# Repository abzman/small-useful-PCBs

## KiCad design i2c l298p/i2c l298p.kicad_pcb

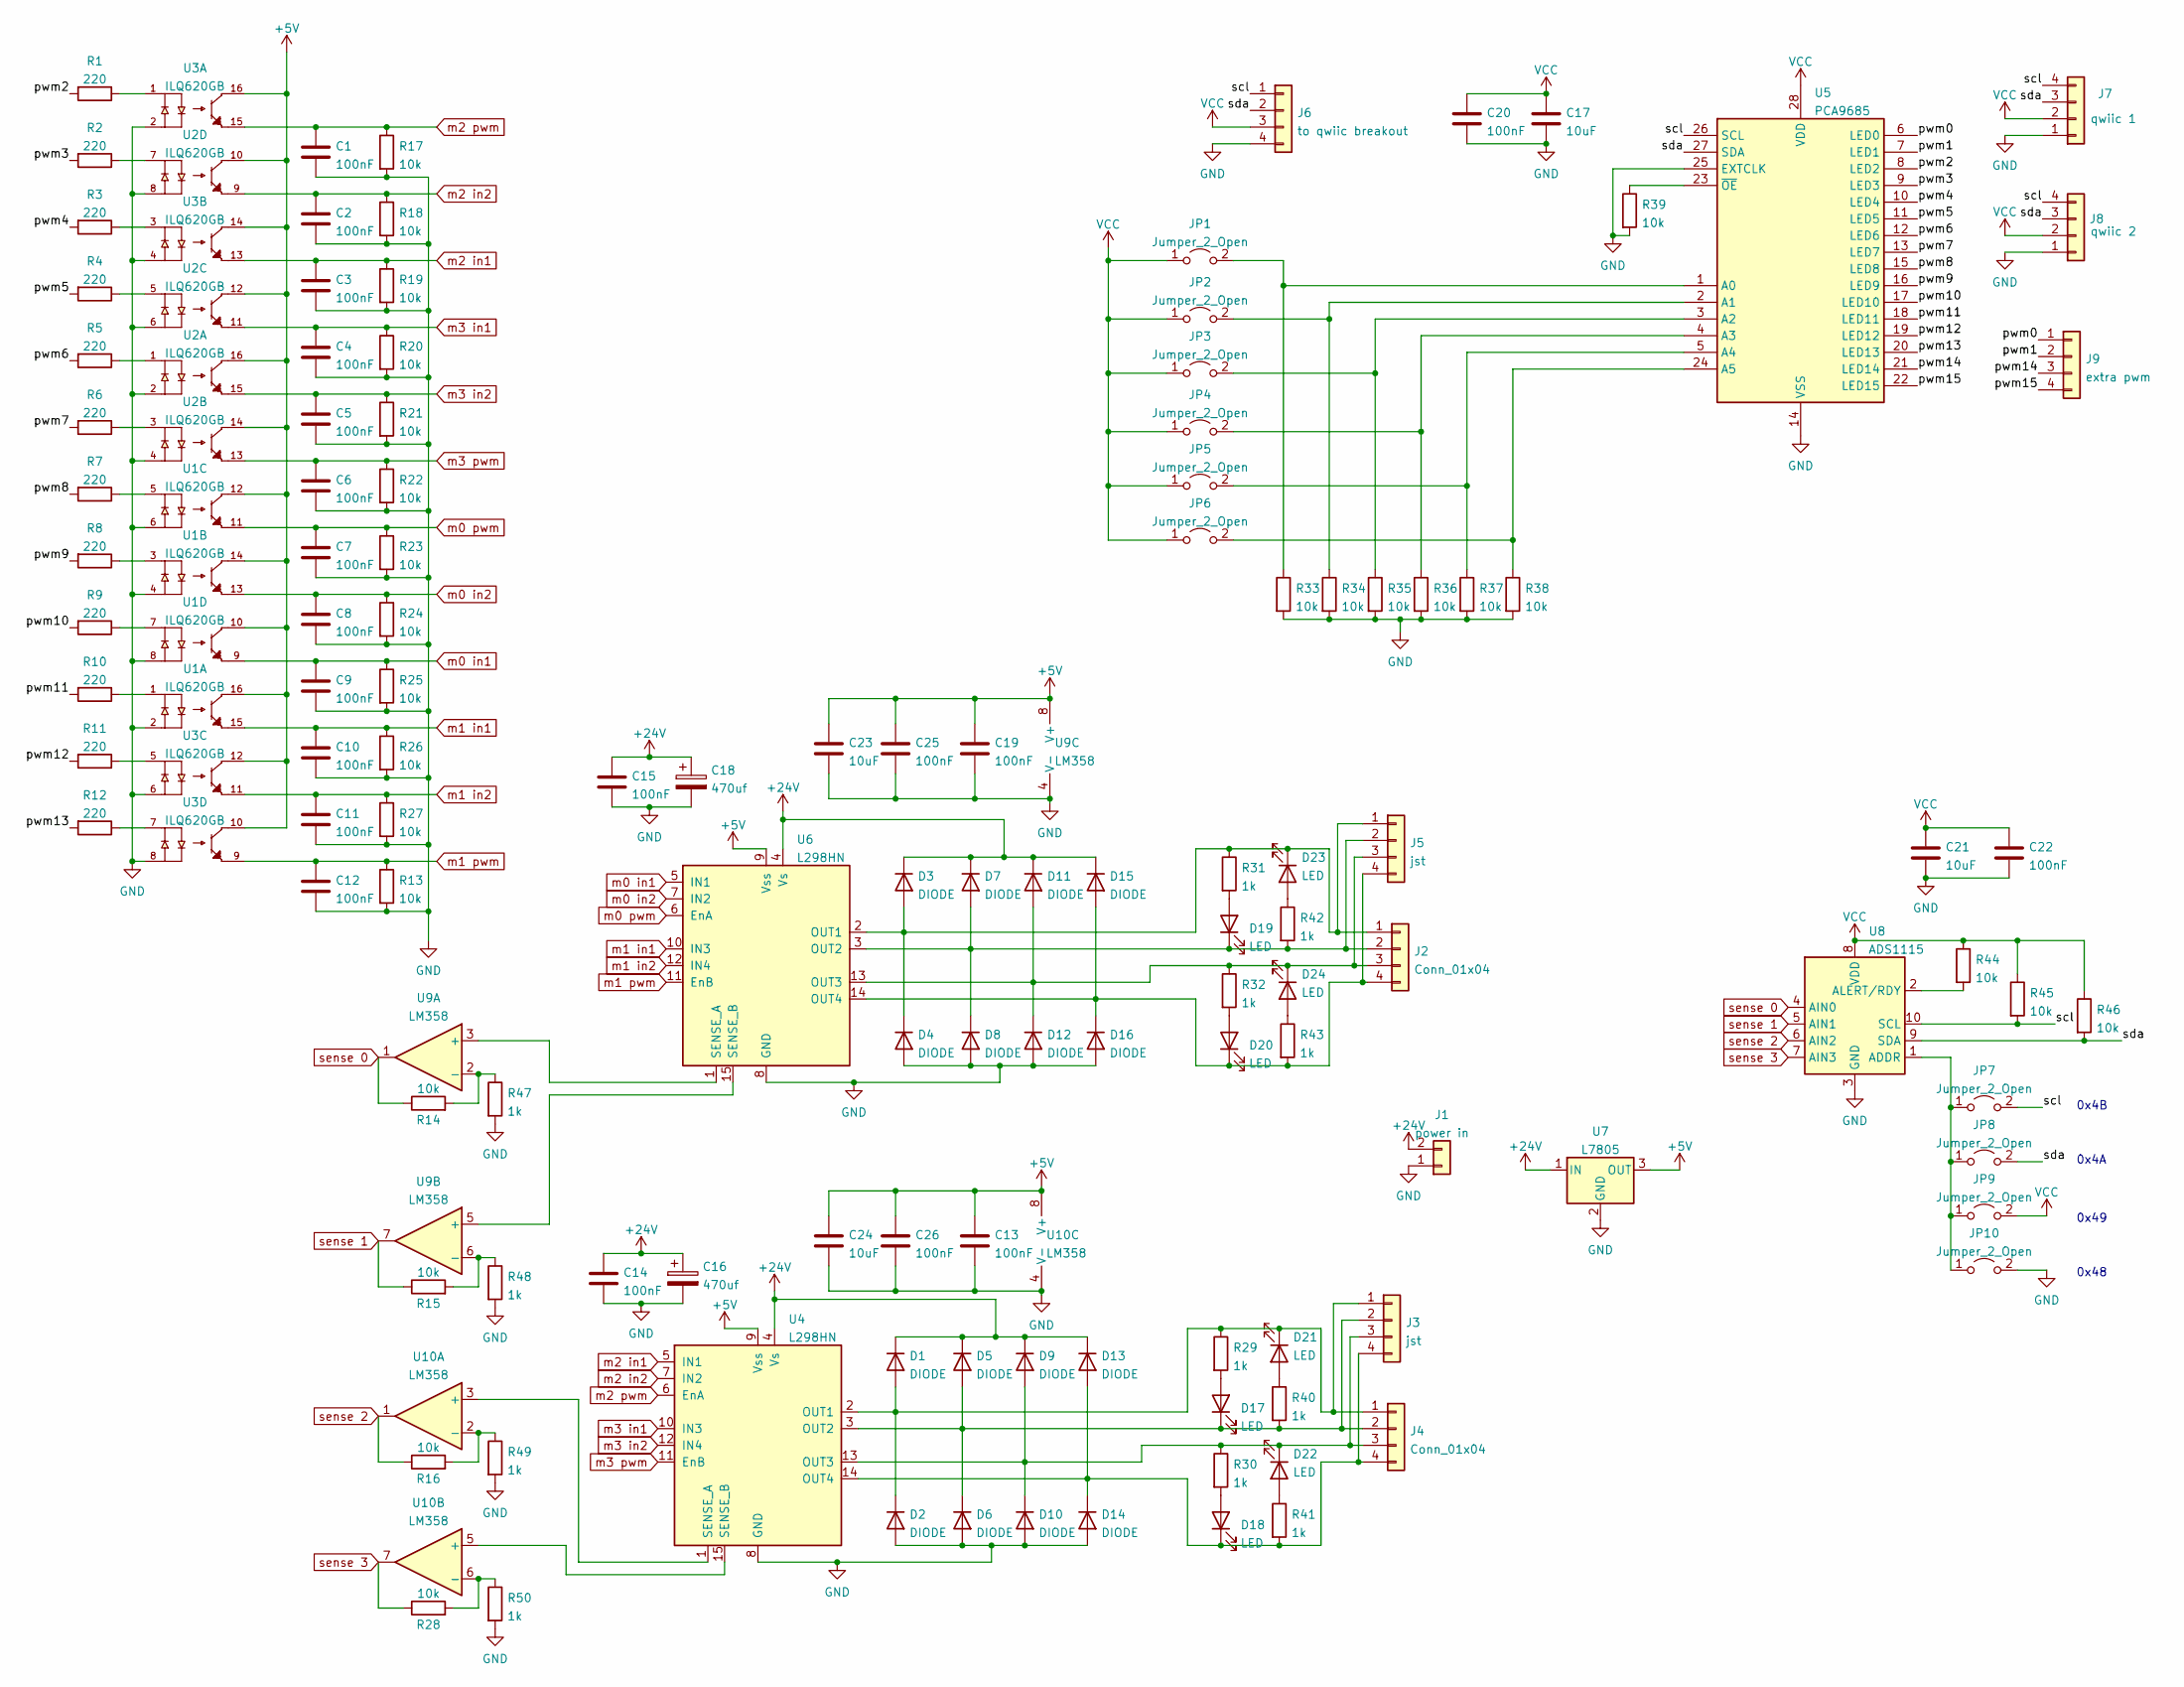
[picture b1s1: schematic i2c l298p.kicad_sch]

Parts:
C1, C2, C3, C4, C5, C6, C7, C8, C9, C10, C11, C12, C13, C14, C15, C19, C20, C22, C25, C26: 100nF; C_0603_1608Metric
C16, C18: 470uf; CP_Radial_D8.0mm_P3.50mm
C17, C21, C23, C24: 10uF; C_0603_1608Metric
D1, D2, D3, D4, D5, D6, D7, D8, D9, D10, D11, D12, D13, D14, D15, D16: DIODE; D_SMA
D17, D18, D19, D20, D21, D22, D23, D24: LED; LED_0603_1608Metric
J1: power in; TerminalBlock_Phoenix_MKDS-1,5-2_1x02_P5.00mm_Horizontal
J2, J4: Conn_01x04; TerminalBlock_Phoenix_MKDS-1,5-4_1x04_P5.00mm_Horizontal
J3, J5: jst; JST_XH_B4B-XH-A_1x04_P2.50mm_Vertical
J6: to qwiic breakout; PinHeader_1x04_P2.54mm_Vertical
J7: qwiic 1; JST_SH_SM04B-SRSS-TB_1x04-1MP_P1.00mm_Horizontal
J8: qwiic 2; JST_SH_SM04B-SRSS-TB_1x04-1MP_P1.00mm_Horizontal
J9: extra pwm; PinHeader_1x04_P2.54mm_Vertical
JP1, JP2, JP3, JP4, JP5, JP7, JP8, JP9, JP10: Jumper_2_Open; SolderJumper-2_P1.3mm_Open_RoundedPad1.0x1.5mm
JP6: Jumper_2_Open; SolderJumper-2_P1.3mm_Bridged_RoundedPad1.0x1.5mm
R1, R2, R3, R4, R5, R6, R7, R8, R9, R10, R11, R12: 220; R_0603_1608Metric
R13, R14, R15, R16, R17, R18, R19, R20, R21, R22, R23, R24, R25, R26, R27, R28, R33, R34, R35, R36, R37, R38, R39, R44, R45, R46: 10k; R_0603_1608Metric
R29, R30, R31, R32, R40, R41, R42, R43, R47, R48, R49, R50: 1k; R_0603_1608Metric
U1, U2, U3: ILQ620GB; OPTO_ILQ620GB-X009; PARTREV 1.8
U4, U6: L298HN; TO-220-15_P2.54x2.54mm_StaggerOdd_Lead4.58mm_Vertical
U5: PCA9685; TSSOP-28_4.4x9.7mm_P0.65mm
U7: L7805; TO-220-3_Horizontal_TabDown
U8: ADS1115; TSSOP-10_3x3mm_P0.5mm
U9, U10: LM358; SOIC-8_3.9x4.9mm_P1.27mm

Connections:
+5V: C13.1, C19.1, C23.1, C24.1, C25.1, C26.1, U1.10, U1.12, U1.14, U1.16, U2.10, U2.12, U2.14, U2.16, U3.10, U3.12, U3.14, U3.16, U4.9 (Vss), U6.9 (Vss), U7.3 (OUT), U9.8 (V+), U10.8 (V+)
+24V: C14.1, C15.1, C16.1, C18.1, D1.2 (K), D3.2 (K), D5.2 (K), D7.2 (K), D9.2 (K), D11.2 (K), D13.2 (K), D15.2 (K), J1.2, U4.4 (Vs), U6.4 (Vs), U7.1 (IN)
/pwm0: J9.1, U5.6 (LED0)
/pwm1: J9.2, U5.7 (LED1)
/pwm2: R1.2, U5.8 (LED2)
/pwm3: R2.2, U5.9 (LED3)
/pwm4: R3.2, U5.10 (LED4)
/pwm5: R4.2, U5.11 (LED5)
/pwm6: R5.2, U5.12 (LED6)
/pwm7: R6.2, U5.13 (LED7)
/pwm8: R7.2, U5.15 (LED8)
/pwm9: R8.2, U5.16 (LED9)
/pwm10: R9.2, U5.17 (LED10)
/pwm11: R10.2, U5.18 (LED11)
/pwm12: R11.2, U5.19 (LED12)
/pwm13: R12.2, U5.20 (LED13)
/pwm14: J9.3, U5.21 (LED14)
/pwm15: J9.4, U5.22 (LED15)
/scl: J6.1, J7.4, J8.4, JP7.2 (B), R45.2, U5.26 (SCL), U8.10 (SCL)
/sda: J6.2, J7.3, J8.3, JP8.2 (B), R46.2, U5.27 (SDA), U8.9 (SDA)
GND: C1.2, C2.2, C3.2, C4.2, C5.2, C6.2, C7.2, C8.2, C9.2, C10.2, C11.2, C12.2, C13.2, C14.2, C15.2, C16.2, C17.2, C18.2, C19.2, C20.2, C21.2, C22.2, C23.2, C24.2, C25.2, C26.2, D2.1 (A), D4.1 (A), D6.1 (A), D8.1 (A), D10.1 (A), D12.1 (A), D14.1 (A), D16.1 (A), J1.1, J6.4, J7.1, J8.1, JP10.2 (B), R13.2, R17.2, R18.2, R19.2, R20.2, R21.2, R22.2, R23.2, R24.2, R25.2, R26.2, R27.2, R33.2, R34.2, R35.2, R36.2, R37.2, R38.2, R39.2, R47.2, R48.2, R49.2, R50.2, U1.2, U1.4, U1.6, U1.8, U2.2, U2.4, U2.6, U2.8, U3.2, U3.4, U3.6, U3.8, U4.8 (GND), U5.14 (VSS), U5.25 (EXTCLK), U6.8 (GND), U7.2 (GND), U8.3 (GND), U9.4 (V-), U10.4 (V-)
unnamed: D1.1 (A), D2.2 (K), D21.1 (K), J3.1, J4.1, R29.1, U4.2 (OUT1)
unnamed: D9.1 (A), D10.2 (K), D22.1 (K), J3.3, J4.3, R30.1, U4.13 (OUT3)
unnamed: D11.1 (A), D12.2 (K), D24.1 (K), J2.3, J5.3, R32.1, U6.13 (OUT3)
unnamed: D13.1 (A), D14.2 (K), D18.1 (K), J3.4, J4.4, R41.2, U4.14 (OUT4)
unnamed: D15.1 (A), D16.2 (K), D20.1 (K), J2.4, J5.4, R43.2, U6.14 (OUT4)
unnamed: D5.1 (A), D6.2 (K), D17.1 (K), J3.2, J4.2, R40.2, U4.3 (OUT2)
unnamed: D17.2 (A), R29.2
unnamed: D18.2 (A), R30.2
unnamed: D7.1 (A), D8.2 (K), D19.1 (K), J2.2, J5.2, R42.2, U6.3 (OUT2)
unnamed: D19.2 (A), R31.2
unnamed: D20.2 (A), R32.2
unnamed: D21.2 (A), R40.1
unnamed: D22.2 (A), R41.1
unnamed: D3.1 (A), D4.2 (K), D23.1 (K), J2.1, J5.1, R31.1, U6.2 (OUT1)
unnamed: D23.2 (A), R42.1
unnamed: D24.2 (A), R43.1
unnamed: JP1.2 (B), R33.1, U5.1 (A0)
unnamed: JP2.2 (B), R34.1, U5.2 (A1)
unnamed: JP3.2 (B), R35.1, U5.3 (A2)
unnamed: JP4.2 (B), R36.1, U5.4 (A3)
unnamed: JP5.2 (B), R37.1, U5.5 (A4)
unnamed: JP6.2 (B), R38.1, U5.24 (A5)
unnamed: JP7.1 (A), JP8.1 (A), JP9.1 (A), JP10.1 (A), U8.1 (ADDR)
unnamed: R1.1, U3.1
unnamed: R2.1, U2.7
unnamed: R3.1, U3.3
unnamed: R4.1, U2.5
unnamed: R5.1, U2.1
unnamed: R6.1, U2.3
unnamed: R7.1, U1.5
unnamed: R8.1, U1.3
unnamed: R9.1, U1.7
unnamed: R10.1, U1.1
unnamed: R11.1, U3.5
unnamed: R12.1, U3.7
unnamed: R14.2, R47.1, U9.2 (-)
unnamed: R15.2, R48.1, U9.6 (-)
unnamed: R16.2, R49.1, U10.2 (-)
unnamed: R28.2, R50.1, U10.6 (-)
unnamed: R39.1, U5.23 (~OE)
unnamed: R44.2, U8.2 (ALERT/RDY)
unnamed: U6.1 (SENSE_A), U9.3 (+)
unnamed: U6.15 (SENSE_B), U9.5 (+)
unnamed: U4.1 (SENSE_A), U10.3 (+)
unnamed: U4.15 (SENSE_B), U10.5 (+)
VCC: C17.1, C20.1, C21.1, C22.1, J6.3, J7.2, J8.2, JP1.1 (A), JP2.1 (A), JP3.1 (A), JP4.1 (A), JP5.1 (A), JP6.1 (A), JP9.2 (B), R44.1, R45.1, R46.1, U5.28 (VDD), U8.8 (VDD)
m0 in1: C9.1, R25.1, U1.9, U6.5 (IN1)
m0 in2: C8.1, R24.1, U1.13, U6.7 (IN2)
m0 pwm: C7.1, R23.1, U1.11, U6.6 (EnA)
m1 in1: C10.1, R26.1, U1.15, U6.10 (IN3)
m1 in2: C11.1, R27.1, U3.11, U6.12 (IN4)
m1 pwm: C12.1, R13.1, U3.9, U6.11 (EnB)
m2 in1: C3.1, R19.1, U3.13, U4.5 (IN1)
m2 in2: C2.1, R18.1, U2.9, U4.7 (IN2)
m2 pwm: C1.1, R17.1, U3.15, U4.6 (EnA)
m3 in1: C4.1, R20.1, U2.11, U4.10 (IN3)
m3 in2: C5.1, R21.1, U2.15, U4.12 (IN4)
m3 pwm: C6.1, R22.1, U2.13, U4.11 (EnB)
sense 0: R14.1, U8.4 (AIN0), U9.1
sense 1: R15.1, U8.5 (AIN1), U9.7
sense 2: R16.1, U8.6 (AIN2), U10.1
sense 3: R28.1, U8.7 (AIN3), U10.7

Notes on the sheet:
0x48
0x4A
0x49
0x4B

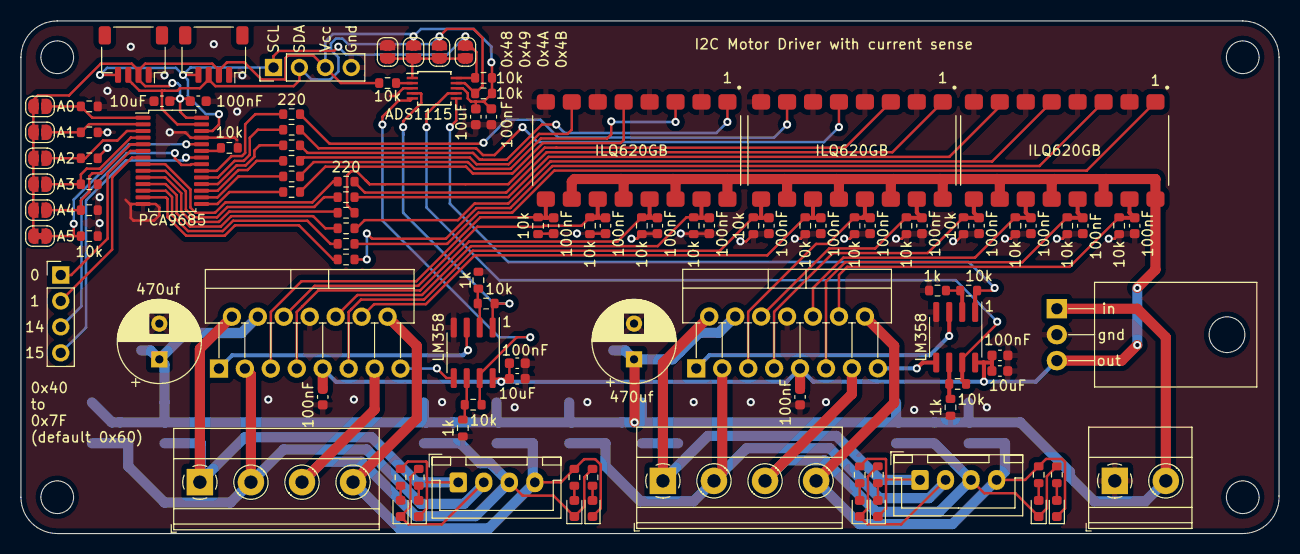
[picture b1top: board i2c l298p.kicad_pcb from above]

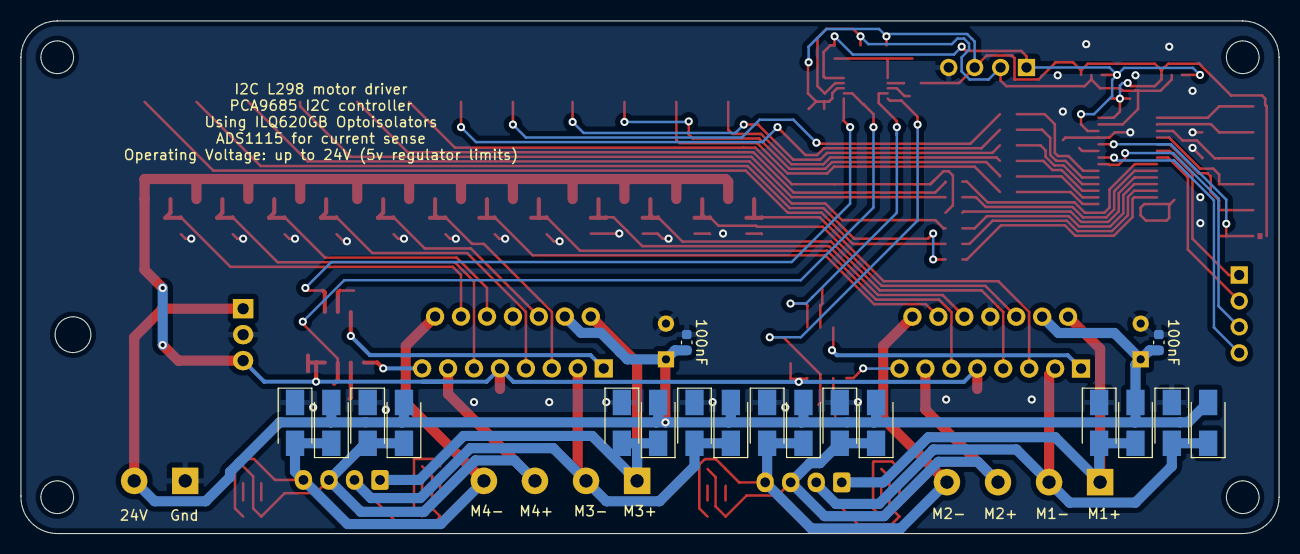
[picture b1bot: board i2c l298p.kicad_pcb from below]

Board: 2 copper layers, 123.2 x 50.2 mm, 129 parts (18 on the bottom side), 83 nets.

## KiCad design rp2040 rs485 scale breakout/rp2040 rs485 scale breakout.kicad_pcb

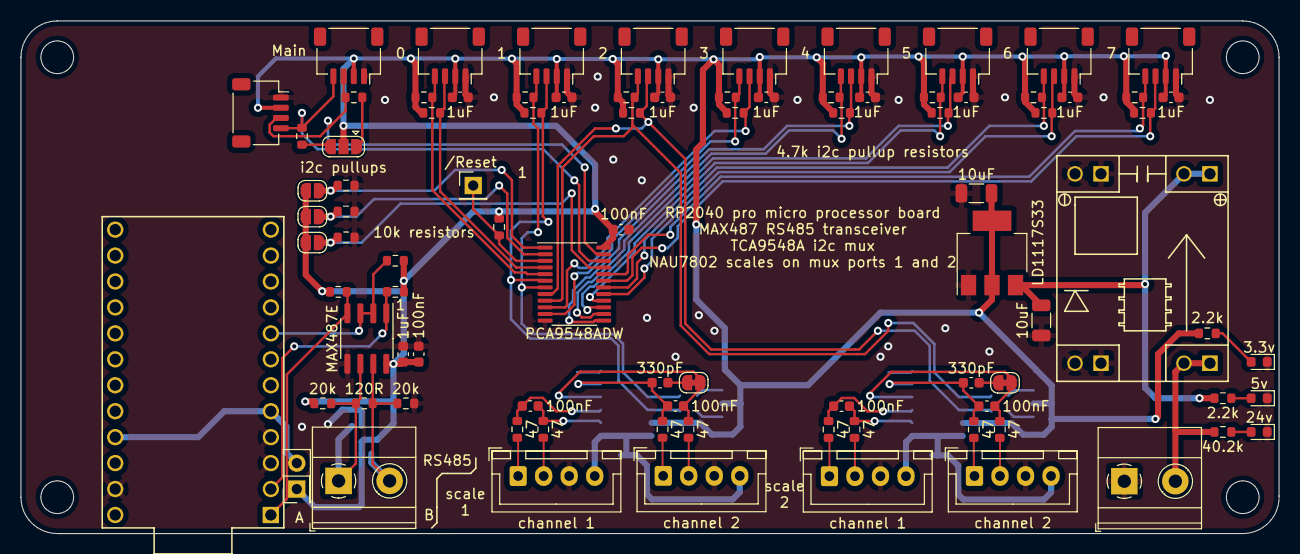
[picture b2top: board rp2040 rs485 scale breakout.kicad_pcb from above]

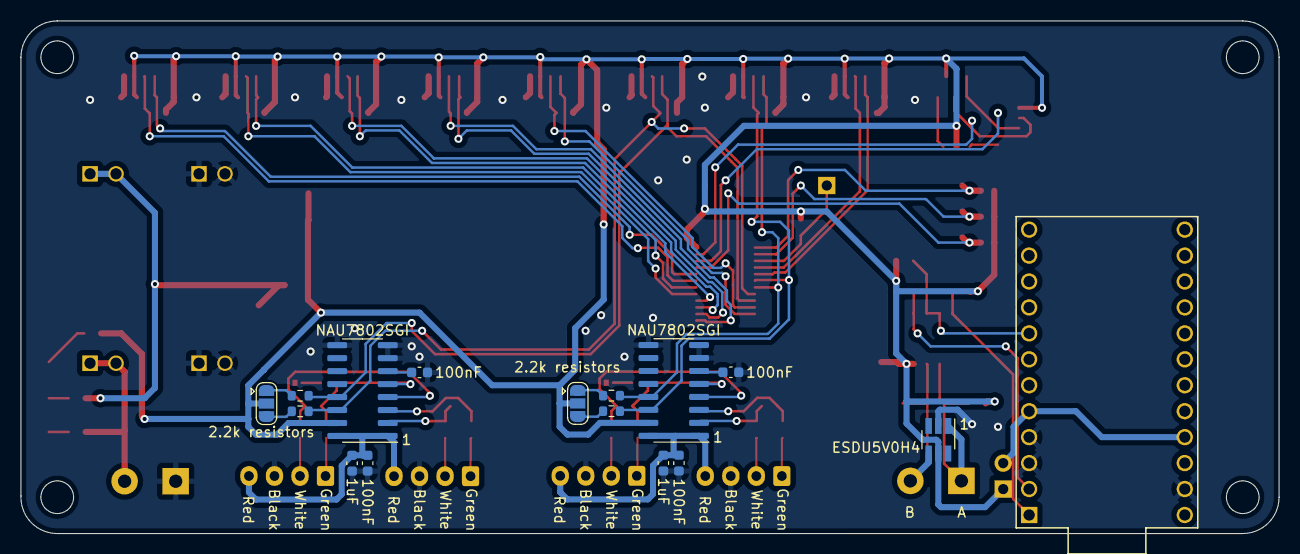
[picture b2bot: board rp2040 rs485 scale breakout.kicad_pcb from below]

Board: 2 copper layers, 123.2 x 50.2 mm, 105 parts (15 on the bottom side), 63 nets.

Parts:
C1, C4, C5, C6, C7, C8, C9, C10, C11, C16, C21: 1uF; C_0603_1608Metric
C2, C3, C13, C14, C15, C18, C19, C20, C22, C23: 100nF; C_0603_1608Metric
C12, C17: 330pF; C_0603_1608Metric
C24, C25: 10uF; C_1206_3216Metric
D1: 24v; LED_0603_1608Metric
D2: 5v; LED_0603_1608Metric
D3: 3.3v; LED_0603_1608Metric
J1: main i2c; JST_SH_SM04B-SRSS-TB_1x04-1MP_P1.00mm_Horizontal
J2: ESDU5V0H4; SOT-23-6_Handsoldering
J3: rs485; TerminalBlock_Phoenix_MKDS-1,5-2_1x02_P5.00mm_Horizontal
J4: Conn_01x01; PinHeader_1x01_P2.54mm_Vertical
J5: i2c pullups; SolderJumper-3_P1.3mm_Open_RoundedPad1.0x1.5mm
J6: qwiic from pro micro; JST_SH_SM04B-SRSS-TB_1x04-1MP_P1.00mm_Horizontal
J7: i2c 5; JST_SH_SM04B-SRSS-TB_1x04-1MP_P1.00mm_Horizontal
J8: i2c 6; JST_SH_SM04B-SRSS-TB_1x04-1MP_P1.00mm_Horizontal
J9: i2c 7; JST_SH_SM04B-SRSS-TB_1x04-1MP_P1.00mm_Horizontal
J10: i2c 3; JST_SH_SM04B-SRSS-TB_1x04-1MP_P1.00mm_Horizontal
J11: i2c 4; JST_SH_SM04B-SRSS-TB_1x04-1MP_P1.00mm_Horizontal
J12: i2c 2; JST_SH_SM04B-SRSS-TB_1x04-1MP_P1.00mm_Horizontal
J13: i2c 0; JST_SH_SM04B-SRSS-TB_1x04-1MP_P1.00mm_Horizontal
J14: i2c 1; JST_SH_SM04B-SRSS-TB_1x04-1MP_P1.00mm_Horizontal
J15, J19: channel 1; JST_XH_B4B-XH-A_1x04_P2.50mm_Vertical
J16, J20: channel 2; JST_XH_B4B-XH-A_1x04_P2.50mm_Vertical
J17, J21: cap; SolderJumper-2_P1.3mm_Bridged_RoundedPad1.0x1.5mm
J18, J22: i2c pullips; SolderJumper-3_P1.3mm_Open_RoundedPad1.0x1.5mm
J23: power in; TerminalBlock_Phoenix_MKDS-1,5-2_1x02_P5.00mm_Horizontal
J24: Conn_01x02; PinHeader_2x01_P2.54mm_Vertical
JP1, JP2, JP3: Jumper_2_Open; SolderJumper-2_P1.3mm_Open_RoundedPad1.0x1.5mm
R1, R2, R3, R4, R8, R9, R10: 10k; R_0603_1608Metric
R5, R7: 20k; R_0603_1608Metric
R6: 120R; R_0603_1608Metric
R11, R12, R13, R14, R15, R16, R17, R18, R19, R20, R21, R22, R23, R24, R25, R26, R27, R28: 4.7k; R_0603_1608Metric
R29, R30, R33, R34, R37, R38, R39, R40: 47; R_0603_1608Metric
R31, R32, R35, R36, R42, R43: 2.2k; R_0603_1608Metric
R41: 40.2k; R_0603_1608Metric
U1: MAX487E; SOIC-8_3.9x4.9mm_P1.27mm
U2: ProMicro_2040; ProMicro
U3: PCA9548ADW; TSSOP-24_4.4x7.8mm_P0.65mm
U4, U5: NAU7802SGI; SOIC-16_3.9x9.9mm_P1.27mm
U6: mp1584 dcdc; MP1584_buck_module
U7: LD1117S33; SOT-223-3_TabPin2

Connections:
485 direction: R2.2, U1.2 (~RE), U1.3 (DE), U2.8 (5)
+3V3: C1.1, C2.1, C3.1, C4.1, C5.1, C6.1, C7.1, C8.1, C9.1, C10.1, C11.1, C25.1, J1.2, J2.5, J5.2, J6.2, J7.2, J8.2, J9.2, J10.2, J11.2, J12.2, J13.2, J14.2, J18.2, J22.2, J24.1, JP1.1 (A), JP2.1 (A), JP3.1 (A), R1.1, R2.1, R3.1, R7.2, R10.1, R13.1, R14.1, R15.1, R16.1, R17.1, R18.1, R19.1, R20.1, R21.1, R22.1, R23.1, R24.1, R25.1, R26.1, R27.1, R28.1, R43.1, U1.8 (VCC), U3.24 (VCC), U4.15 (DVDD), U5.15 (DVDD), U7.2 (VO)
+5V: C24.1, R42.1, U6.4, U7.3 (VI)
+24V: J23.2, R41.1, U6.1
/nau7802 module1/A+: J19.1, R34.1
/nau7802 module1/A-: J19.2, R33.1
/nau7802 module1/B+: J20.1, R40.1
/nau7802 module1/B-: J20.2, R39.1
/nau7802 module/A+: J15.1, R30.1
/nau7802 module/A-: J15.2, R29.1
/nau7802 module/B+: J16.1, R38.1
/nau7802 module/B-: J16.2, R37.1
A: J2.1, J3.1, R6.2, R7.1, U1.6 (A)
A0: JP1.2 (B), R4.1, U3.1 (A0)
A1: JP2.2 (B), R8.1, U3.2 (A1)
A2: JP3.2 (B), R9.1, U3.21 (A2)
B: J2.4, J3.2, R5.2, R6.1, U1.7 (B)
GND: C1.2, C2.2, C3.2, C4.2, C5.2, C6.2, C7.2, C8.2, C9.2, C10.2, C11.2, C14.2, C15.2, C16.2, C19.2, C20.2, C21.2, C24.2, C25.2, D1.1 (K), D2.1 (K), D3.1 (K), J1.1, J2.2, J6.1, J7.1, J8.1, J9.1, J10.1, J11.1, J12.1, J13.1, J14.1, J15.3, J16.3, J19.3, J20.3, J23.1, R4.2, R5.1, R8.2, R9.2, U1.5 (GND), U2.3 (GND), U2.4 (GND), U2.23 (GND), U3.12 (GND), U4.7 (REFN), U4.8 (AVSS), U4.9 (DVSS), U5.7 (REFN), U5.8 (AVSS), U5.9 (DVSS), U6.2, U6.3, U7.1 (GND)
Main_SCL: J1.4, J6.4, R11.2, U3.22 (SCL)
Main_SDA: J1.3, J6.3, R12.2, U3.23 (SDA)
unnamed: C12.1, J17.1
unnamed: C12.2, C22.2, R38.2, U4.5 (VIN2P)
unnamed: C13.1, R29.2, U4.2 (VIN1N)
unnamed: C13.2, R30.2, U4.3 (VIN1P)
unnamed: C14.1, U4.6 (VBG)
unnamed: C15.1, C16.1, J15.4, J16.4, U4.1 (REFP), U4.16 (AVDD/LDO)
unnamed: C17.1, J21.1
unnamed: C17.2, C23.2, R40.2, U5.5 (VIN2P)
unnamed: C18.1, R33.2, U5.2 (VIN1N)
unnamed: C18.2, R34.2, U5.3 (VIN1P)
unnamed: C19.1, U5.6 (VBG)
unnamed: C20.1, C21.1, J19.4, J20.4, U5.1 (REFP), U5.16 (AVDD/LDO)
unnamed: C22.1, J17.2, R37.2, U4.4 (VIN2N)
unnamed: C23.1, J21.2, R39.2, U5.4 (VIN2N)
unnamed: D1.2 (A), R41.2
unnamed: D2.2 (A), R42.2
unnamed: D3.2 (A), R43.2
unnamed: J4.1, R10.2, U3.3 (~RESET)
unnamed: J5.1, R12.1
unnamed: J5.3, R11.1
unnamed: J18.1, R31.1
unnamed: J18.3, R32.1
unnamed: J22.1, R35.1
unnamed: J22.3, R36.1
unnamed: J24.2, U2.5 (2), U2.21 (3.3v)
Rx: R3.2, U1.1 (RO), U2.2 (RX)
SCL0: J13.4, R22.2, U3.5 (SC0)
SCL1: J14.4, R23.2, R31.2, U3.7 (SC1), U4.13 (SCLK)
SCL2: J12.4, R21.2, R35.2, U3.9 (SC2), U5.13 (SCLK)
SCL3: J10.4, R19.2, U3.11 (SC3)
SCL4: J11.4, R20.2, U3.14 (SC4)
SCL5: J7.4, R13.2, U3.16 (SC5)
SCL6: J8.4, R14.2, U3.18 (SC6)
SCL7: J9.4, R15.2, U3.20 (SC7)
SDA0: J13.3, R27.2, U3.4 (SD0)
SDA1: J14.3, R28.2, R32.2, U3.6 (SD1), U4.14 (SDIO)
SDA2: J12.3, R26.2, R36.2, U3.8 (SD2), U5.14 (SDIO)
SDA3: J10.3, R24.2, U3.10 (SD3)
SDA4: J11.3, R25.2, U3.13 (SD4)
SDA5: J7.3, R16.2, U3.15 (SD5)
SDA6: J8.3, R17.2, U3.17 (SD6)
SDA7: J9.3, R18.2, U3.19 (SD7)
Tx: R1.2, U1.4 (DI), U2.1 (TX)

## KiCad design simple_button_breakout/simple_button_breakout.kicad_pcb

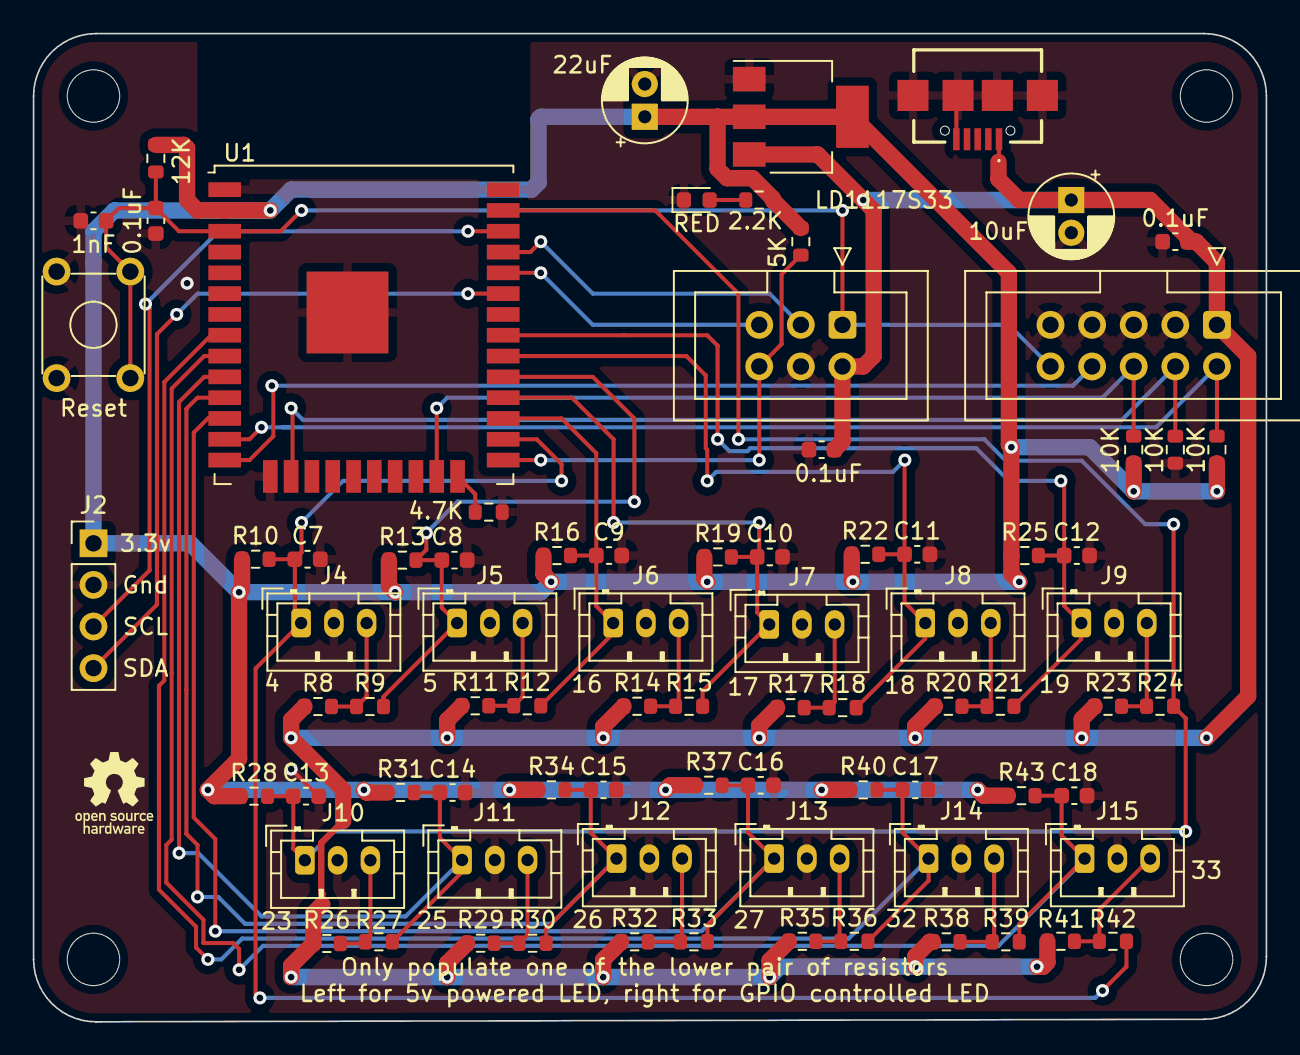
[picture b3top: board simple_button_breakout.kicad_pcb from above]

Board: 2 copper layers, 75.3 x 60.3 mm, 81 parts (0 on the bottom side), 39 nets.

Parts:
C1, C3, C6: 0.1uF; C_0603_1608Metric
C2: 1nF; C_0603_1608Metric
C4: 10uF; CP_Radial_D5.0mm_P2.00mm
C5: 22uF; CP_Radial_D5.0mm_P2.00mm
C7, C8, C9, C10, C11, C12, C13, C14, C15, C16, C17, C18: Cfilter; C_0603_1608Metric
D1: RED; LED_0603_1608Metric
J1: Conn_02x05_Odd_Even; IDC-Header_2x05_P2.54mm_Vertical
J2: bme280; PinHeader_1x04_P2.54mm_Vertical
J3: Conn_02x03_Odd_Even; IDC-Header_2x03_P2.54mm_Vertical
J4, J5, J6, J7, J8, J9, J10, J11, J12, J13, J14, J15: Conn_01x03; JST_PH_B3B-PH-K_1x03_P2.00mm_Vertical
J16: UJ2-MIBH-G-SMT-TR; UJ2MIBHGSMTTR
R1: 12K; R_0603_1608Metric
R2, R5, R6: 10K; R_0603_1608Metric
R3: 4.7K; R_0603_1608Metric
R4: 2.2K; R_0603_1608Metric
R7: 5K; R_0603_1608Metric
R8, R11, R14, R17, R20, R23, R26, R29, R32, R35, R38, R41: R5v; R_0603_1608Metric
R9, R12, R15, R18, R21, R24, R27, R30, R33, R36, R39, R42: Rgpio; R_0603_1608Metric
R10, R13, R16, R19, R22, R25, R28, R31, R34, R37, R40, R43: Rfilter; R_0603_1608Metric
SW1: SW_MEC_5E; SW_TH_Tactile_Omron_B3F-10xx
U1: ESP32-WROOM-32U
U2: LD1117S33TR_SOT223; SOT-223-3_TabPin2

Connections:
+3V3: C5.1, J2.1, R1.1, R2.2, R4.1, R6.2, R7.1, R10.1, R13.1, R16.1, R19.1, R22.1, R25.1, R28.1, R31.1, R34.1, R37.1, R40.1, R43.1, U1.2 (VDD), U2.2 (VO)
+5V: C1.1, C4.1, C6.1, J1.1, J3.2, J16.1, R8.1, R11.1, R14.1, R17.1, R20.1, R23.1, R26.1, R29.1, R32.1, R35.1, R38.1, R41.1, U2.3 (VI)
/ESP_EN: C2.2, C3.1, J1.10, J3.1, R1.2, SW1.3 (K), SW1.4 (A), U1.3 (EN)
/ESP_IO0: J3.6, R7.2, U1.25 (IO0)
/ESP_IO1: J3.3, U1.35 (TXD0/IO1)
/ESP_IO2: R3.1, U1.24 (IO2)
/ESP_IO3: J3.5, U1.34 (RXD0/IO3)
/ESP_IO4: C7.1, J4.1, R10.2, R42.2, U1.26 (IO4)
/ESP_IO5: C8.1, J5.1, R9.2, R13.2, U1.29 (IO5)
/ESP_IO12: J1.8, U1.14 (IO12)
/ESP_IO13: J1.4, R5.1, U1.16 (IO13)
/ESP_IO14: J1.2, R2.1, U1.13 (IO14)
/ESP_IO15: J1.6, R6.1, U1.23 (IO15)
/ESP_IO16: C9.1, J6.1, R12.2, R16.2, U1.27 (IO16)
/ESP_IO17: C10.1, J7.1, R15.2, R19.2, U1.28 (IO17)
/ESP_IO18: C11.1, J8.1, R18.2, R22.2, U1.30 (IO18)
/ESP_IO19: C12.1, J9.1, R21.2, R25.2, U1.31 (IO19)
/ESP_IO21: J2.4, U1.33 (IO21)
/ESP_IO22: J2.3, U1.36 (IO22)
/ESP_IO23: C13.1, J10.1, R24.2, R28.2, U1.37 (IO23)
/ESP_IO25: C14.1, J11.1, R27.2, R31.2, U1.10 (IO25)
/ESP_IO26: C15.1, J12.1, R30.2, R34.2, U1.11 (IO26)
/ESP_IO27: C16.1, J13.1, R33.2, R37.2, U1.12 (IO27)
/ESP_IO32: C17.1, J14.1, R36.2, R40.2, U1.8 (IO32)
/ESP_IO33: C18.1, J15.1, R39.2, R43.2, U1.9 (IO33)
GND: C1.2, C2.1, C3.2, C4.2, C5.2, C6.2, C7.2, C8.2, C9.2, C10.2, C11.2, C12.2, C13.2, C14.2, C15.2, C16.2, C17.2, C18.2, D1.1 (K), J1.3, J1.5, J1.7, J1.9, J2.2, J3.4, J4.2, J5.2, J6.2, J7.2, J8.2, J9.2, J10.2, J11.2, J12.2, J13.2, J14.2, J15.2, J16.2, J16.MP1, J16.MP2, J16.MP3, J16.MP4, R3.2, R5.2, SW1.1, SW1.2, U1.1 (GND), U1.15 (GND), U1.38 (GND), U1.39 (GND), U2.1 (GND)
unnamed: D1.2 (A), R4.2
unnamed: J4.3, R8.2, R9.1
unnamed: J5.3, R11.2, R12.1
unnamed: J6.3, R14.2, R15.1
unnamed: J7.3, R17.2, R18.1
unnamed: J8.3, R20.2, R21.1
unnamed: J9.3, R23.2, R24.1
unnamed: J10.3, R26.2, R27.1
unnamed: J11.3, R29.2, R30.1
unnamed: J12.3, R32.2, R33.1
unnamed: J13.3, R35.2, R36.1
unnamed: J14.3, R38.2, R39.1
unnamed: J15.3, R41.2, R42.1

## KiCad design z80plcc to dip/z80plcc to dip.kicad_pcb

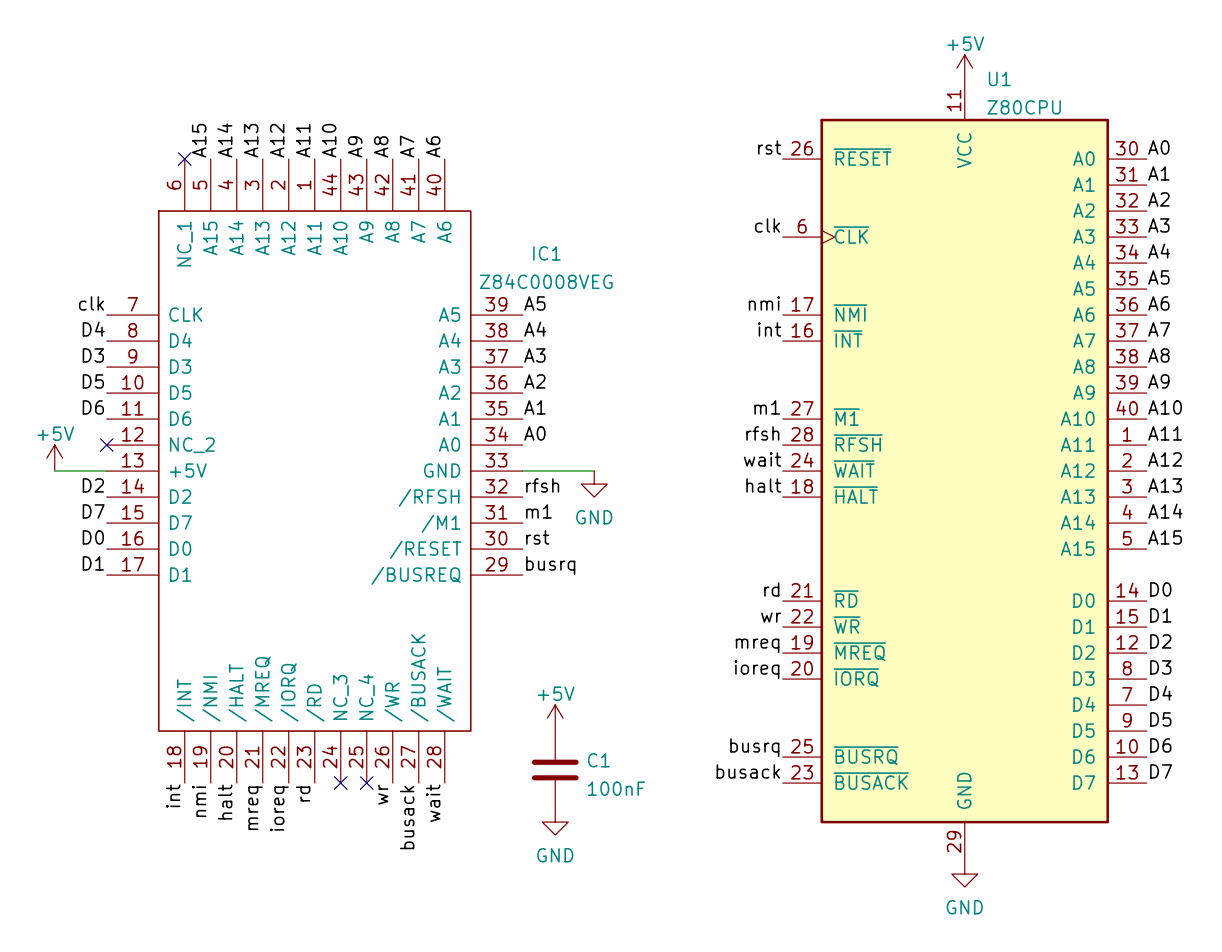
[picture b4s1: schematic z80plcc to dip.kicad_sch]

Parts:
C1: 100nF; C_0603_1608Metric
IC1: Z84C0008VEG; PLCC127P1750X1750X457-44N; Manufacturer_Part_Number Z84C0008VEG
U1: Z80CPU; DIP-40_W15.24mm_Socket

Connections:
+5V: C1.1, IC1.13 (+5V), U1.11 (VCC)
/A0: IC1.34 (A0), U1.30 (A0)
/A1: IC1.35 (A1), U1.31 (A1)
/A2: IC1.36 (A2), U1.32 (A2)
/A3: IC1.37 (A3), U1.33 (A3)
/A4: IC1.38 (A4), U1.34 (A4)
/A5: IC1.39 (A5), U1.35 (A5)
/A6: IC1.40 (A6), U1.36 (A6)
/A7: IC1.41 (A7), U1.37 (A7)
/A8: IC1.42 (A8), U1.38 (A8)
/A9: IC1.43 (A9), U1.39 (A9)
/A10: IC1.44 (A10), U1.40 (A10)
/A11: IC1.1 (A11), U1.1 (A11)
/A12: IC1.2 (A12), U1.2 (A12)
/A13: IC1.3 (A13), U1.3 (A13)
/A14: IC1.4 (A14), U1.4 (A14)
/A15: IC1.5 (A15), U1.5 (A15)
/D0: IC1.16 (D0), U1.14 (D0)
/D1: IC1.17 (D1), U1.15 (D1)
/D2: IC1.14 (D2), U1.12 (D2)
/D3: IC1.9 (D3), U1.8 (D3)
/D4: IC1.8 (D4), U1.7 (D4)
/D5: IC1.10 (D5), U1.9 (D5)
/D6: IC1.11 (D6), U1.10 (D6)
/D7: IC1.15 (D7), U1.13 (D7)
/busack: IC1.27 (/BUSACK), U1.23 (~BUSACK)
/busrq: IC1.29 (/BUSREQ), U1.25 (~BUSRQ)
/clk: IC1.7 (CLK), U1.6 (~CLK)
/halt: IC1.20 (/HALT), U1.18 (~HALT)
/int: IC1.18 (/INT), U1.16 (~INT)
/ioreq: IC1.22 (/IORQ), U1.20 (~IORQ)
/m1: IC1.31 (/M1), U1.27 (~M1)
/mreq: IC1.21 (/MREQ), U1.19 (~MREQ)
/nmi: IC1.19 (/NMI), U1.17 (~NMI)
/rd: IC1.23 (/RD), U1.21 (~RD)
/rfsh: IC1.32 (/RFSH), U1.28 (~RFSH)
/rst: IC1.30 (/RESET), U1.26 (~RESET)
/wait: IC1.28 (/WAIT), U1.24 (~WAIT)
/wr: IC1.26 (/WR), U1.22 (~WR)
GND: C1.2, IC1.33 (GND), U1.29 (GND)

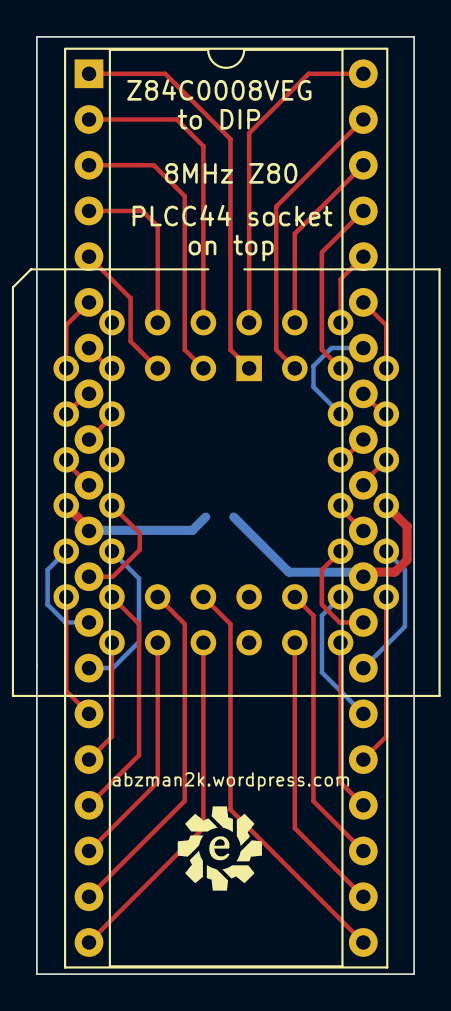
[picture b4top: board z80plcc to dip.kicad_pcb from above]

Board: 2 copper layers, 21.0 x 52.1 mm, 3 parts (1 on the bottom side), 40 nets.
